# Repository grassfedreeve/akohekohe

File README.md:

# ʻākohekohe
26-key, column-staggered, unibody-split keyboard made with [ergogen](https://github.com/ergogen/ergogen) and [KiCad](https://www.kicad.org/). Named after the [ʻākohekohe bird](https://www.mauiforestbirds.org/akohekohe/), (“AH-kohay-kohay”), consider donating to the Maui Forest Bird Recovery Project. 

Basically a ZilpZalp with thumbs cut off, and the most comfortable layout I have found. 

Two versions for choc switches are available:
- The default-spacing solder-only version with silkscreen art and the [original without art](https://github.com/grassfedreeve/akohekohe/blob/main/pcb/gerbers-original.zip) (in the [pcb](https://github.com/grassfedreeve/akohekohe/tree/main/pcb) directory)
- The minimal-choc-spacing solder-only version with the tightest spacing that choc V1 switches allow for (in the [pcb_min_choc](https://github.com/grassfedreeve/akohekohe/tree/main/pcb_min_choc) directory)
  **Note:** You will have to procure min-spacing keycaps. I am not aware of any commercial solution. Recommendation: [Philadelphia Minimalist](https://github.com/pseudoku/PseudoMakeMeKeyCapProfiles/blob/master/Philadelphia_Minimalist.scad) by [Pseudoku](https://github.com/pseudoku). There are also currently no 1.5u min-space keycaps, these will need to be generated.

**Warning:** The min-choc-spacing version has not been tested yet!

# Keymap
Example keymap for how you might use this many keys, created using caksoylar's great [keymap-drawer](https://github.com/caksoylar/keymap-drawer)

Alternative base layouts, Colemak DH, [Bird](https://github.com/jcmkk3/bird-layout), and a Gallium mod shared to me by [ssbb](https://github.com/ssbb) are also great options:

## BOM
- 1 pcb
- 1 Seeed XIAO compatible controller
- 26 sod123 diodes
- 26 kailh choc low profile switches
- 26 keycaps

wireless parts (optional)
- [45mAh 351020 battery](https://www.ebay.com.au/itm/175319348479)
- [5mm pogo pin](https://www.aliexpress.com/item/1005006095992803.html?spm=a2g0o.order_list.order_list_main.35.78fd1802qp0XdF)
- [jumper](https://www.aliexpress.com/item/32827199777.html?spm=a2g0o.order_list.order_list_main.30.78fd1802qp0XdF)
## Firmware
ZMK is what I use and have setup a module for: [ākohekohe ZMK Module](https://github.com/grassfedreeve/zmk-keyboards-akohekohe) 
That being said the matrix is the same as a Hummingbird so you can use hummingbird firmware just fine on whichever firmware you enjoy.

## Art
perce came in and saved the day with amazing art for my keyboards, some quick photos of this are below:

## Inspiration & Thanks
- perce for making the stunning artwork | [madebyperce](https://madebyperce.com/) | [kofi](https://ko-fi.com/madebyperce)
- jcmkk3's [rufous](https://github.com/jcmkk3/trochilidae#rufous) hummingbird variation. Of which I used the Ergogen config, routing, and footprints.
- apfel's [zilpzalp](https://github.com/kilipan/zilpzalp) keyboard
- PJE66's [hummingbird](https://github.com/PJE66/hummingbird) keyboard
- Weteor's [grumpy](https://github.com/weteor/Grumpy) and [fitis](https://github.com/weteor/fitis)
- apsu's [aptmak](https://github.com/apsu/aptmak) keyboard layout

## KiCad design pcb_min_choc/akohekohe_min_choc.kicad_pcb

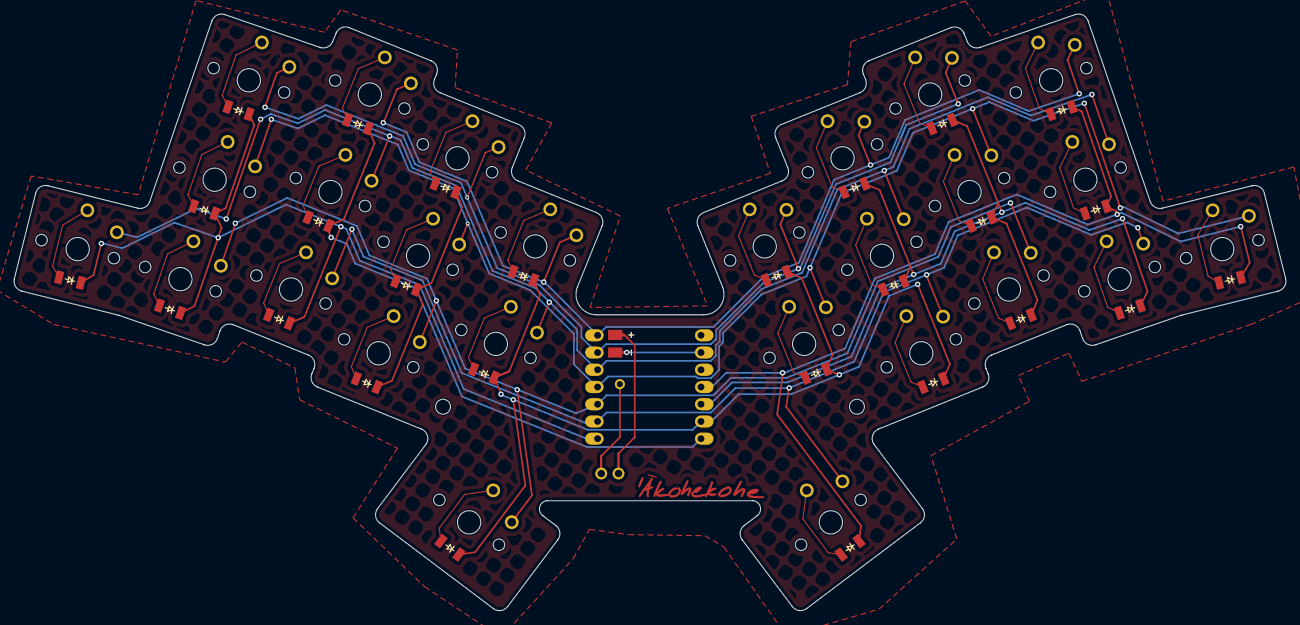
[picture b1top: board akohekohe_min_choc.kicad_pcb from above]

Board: 2 copper layers, 187.5 x 87.9 mm, 31 parts (0 on the bottom side), 12 nets.

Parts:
BT1: Battery_Cell; BatteryPadsReversible
D9: Val**; HeaderJumperSimple
PAD1, PAD1#2: MountingHole_2.2mm_M2
S1, S2, S3, S4, S5, S6, S7, S8, S9, S10, S11, S12, S13, S14, S15, S16, S17, S18, S19, S20, S21, S22, S23, S24, S25, S26: ChocSimpleDiode
U1: xiao; xiao-tht

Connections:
GND: BT1.2, U1.13 (GND)
P0: S7.1, S12.1, S16.1, S22.1, U1.1 (A2)
P1: S4.1, S10.1, S19.1, S24.1, U1.2 (A4)
P2: S1.1, S6.1, S11.1, S15.1, S21.1, U1.3 (A10)
P3: S3.1, S9.1, S13.1, S18.1, S23.1, U1.4 (A11)
P4: S2.1, S8.1, S17.1, S25.1, U1.5 (A8_SDA)
P5: S5.1, S14.1, S20.1, S26.1, U1.6 (A9_SCL)
P6: S1.2, S2.2, S3.2, S4.2, S5.2, U1.7 (B8_TX)
P7: S6.2, S7.2, S8.2, S9.2, S10.2, U1.8 (B9_RX)
P8: S11.2, S12.2, S20.2, S23.2, S24.2, S25.2, U1.9 (A7_SCK)
P9: S14.2, S17.2, S18.2, S19.2, S21.2, S22.2, U1.10 (A5_MISO)
P10: S13.2, S15.2, S16.2, S26.2, U1.11 (A6_MOSI)

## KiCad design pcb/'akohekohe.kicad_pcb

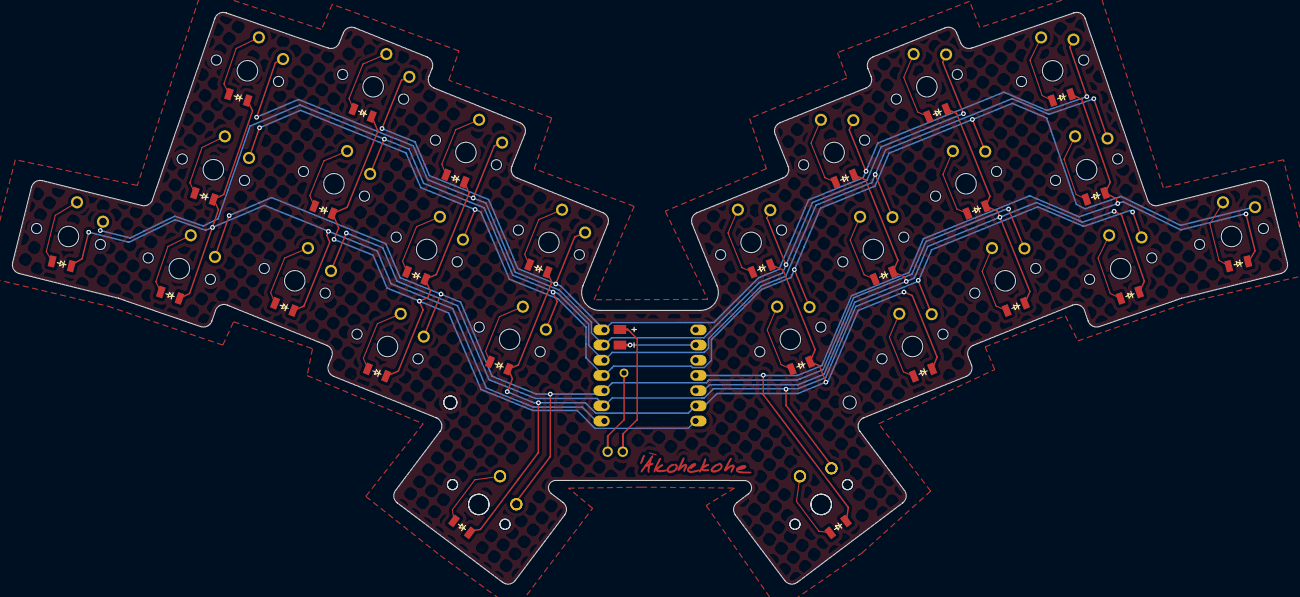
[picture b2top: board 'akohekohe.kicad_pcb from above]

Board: 2 copper layers, 213.3 x 95.6 mm, 34 parts (0 on the bottom side), 12 nets.

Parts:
BT1: Battery_Cell; BatteryPadsReversible
D9: Val**; HeaderJumperSimple
PAD1, PAD1#2, PAD1#3: MountingHole_2.2mm_M2
S25, S26: PG1350
SW1, SW2, SW3, SW4, SW5, SW6, SW7, SW8, SW9, SW10, SW11, SW12, SW17, SW18, SW19, SW20, SW21, SW22, SW23, SW24, SW25, SW26, SW27, SW28: SW_Push; ChocSimpleDiode
SW14, SW15: SW_Push; ChocSimpleDiode 1.5u
U1: xiao; xiao-tht

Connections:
GND: BT1.2, U1.13 (GND)
P0: SW2.1, SW4.1, SW26.1, SW28.1, U1.1 (A2)
P1: SW1.1, SW3.1, SW25.1, SW27.1, U1.2 (A4)
P2: SW6.1, SW8.1, SW9.1, SW22.1, SW24.1, U1.3 (A10)
P3: SW5.1, SW7.1, SW20.1, SW21.1, SW23.1, U1.4 (A11)
P4: S25.1, SW10.1, SW12.1, SW14.1, SW18.1, U1.5 (A8_SDA)
P5: S26.1, SW11.1, SW15.1, SW17.1, SW19.1, U1.6 (A9_SCL)
P6: SW1.2, SW5.2, SW9.2, SW10.2, SW11.2, U1.7 (B8_TX)
P7: SW2.2, SW3.2, SW6.2, SW7.2, SW12.2, U1.8 (B9_RX)
P8: S25.2, SW4.2, SW8.2, SW14.2, SW17.2, SW21.2, SW25.2, U1.9 (A7_SCK)
P9: SW18.2, SW19.2, SW22.2, SW23.2, SW26.2, SW27.2, U1.10 (A5_MISO)
P10: S26.2, SW15.2, SW20.2, SW24.2, SW28.2, U1.11 (A6_MOSI)

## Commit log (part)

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2024-08-06 Update Photo
2024-08-08 add bird/colemak base layouts
2024-08-08 Add Bird & Colemak to README
2024-08-22 update images and read me
2024-08-22 update image
2024-08-22 Fix README.md
2024-09-03 Update keymap
2024-09-05 add firmware submodule zmk-keyboards-akohekohe
2024-09-08 add choc-min pcb and update readme
2024-09-08 update readme again
2024-09-08 ran DRC and fixed minspace
2024-09-19 update firmware submodule
2024-10-10 license
2025-04-14 silkscreen art <3 THANK YOU PERCE
2025-04-14 readme update
2025-04-18 final art & 3 pin
